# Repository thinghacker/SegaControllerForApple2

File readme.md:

# SegaControllerForApple2

Use a Sega Genesis/Megadrive Gamepad with your Apple 2 Computer

This repo contains the PCB details and Arduino code to be able to connect a 3 or 6 button Sega Genesis or Megadrive Gamepad to an Apple 2 Computer which utilises and Arduino Nano v3 and uses Sega Controller code by [Jon Thysell](https://github.com/jonthysell/SegaController) 

[PCB Details including Bill of Materials](pcb)

[Arduino Source Code](source)

## Theory of Operation
Apple 2 computers use two RC timer circuits to determine the position of each joystick axis. The capacitors are within the Apple 2 itself, while the resistors are variable potentiometers within the joystick.  Apple 2 computers expect the joystick to have two 150KOhm pots for X (0 = Left, 150K = Right) and Y (0 = Up, 150K = Down)

This board uses two daisy-chained MCP42100s as a means to create a 200K pot for X and Y (software limit this to 150K +/- any calibration offsets).  As this is an analog circuit, characteristics of the circuitry probably has been changed since the Apple 2 came from the factory, meaning that it is generally necessary to include an offset to wanted values for proper centering (similar to the trimmer capability on original Apple analog sticks) 

The Arduino reads the Sega Gamepad and sets the pot values to simulate analog behavior depending on the emulated joystick mode and previous states (there is a digital mode two analog styles and a hybrid mode which are selectable by clicking the Sega Controller Start Button)

Transistors are uses as switches by the arduino to trigger firebutton 0 and 1 (the method used is based on the [diagram](http://apple2.org.za/gswv/a2zine/faqs/R030PCA2RF.GIF) which was originally posted at in the official Csa2 (comp.sys.apple2) Usenet newsgroup Apple II FAQs)

If installed, the OLED provides visual feedback into the joystick operational mode and indication as to the joystick fire button and analog pot positions.

Audible feedback is also provided through the Piezo Buzzer which can be helpful when executing changes in the middle of a game.

### Gamepad Button Functions

|Button              | Game Pad Mode  | When C is Held Down |
| ------------ | ------------ |------------ |
| A | Firebutton 0 | Firebutton 0 Auto Fire Toggle | 
| B | Firebutton 1 | Firebutton 1 Auto Fire Toggle |
| C | Return Joystick Axes to Centre | |
| Start | Cycle Gamepad modes (Digital, Analog1, Analog2, Hybrid) | Enter Calibration Mode|
| X | Not Used |  |
| Y | Not Used |  |
| Z | Not Used |  |
| Mode | Not Used |  |

#### Notes:
Holding A/B/C together to swap Firebutton 0 and Firebutton 1

While Analog1, Analog2 and Hybrid do not re-centre when the Dpad buttons are released, pressing button C will recentre the stick.

## Calibration Mode

holding <strong>C</strong> and pressing <strong>Start</strong> on the controller will enable calibration mode.

Using the Dpad, the centre offset can be adjusted as necessary. Pressing <strong>Start</strong> will save the calibration offsets into the Arduino EEPROM and return to normal joystick mode

[ComputerInspector (MECC 1.0)](https://ftp.apple.asimov.net/images/disk_utils/diagnostics/ComputerInspector%20%28MECC%201.0%29.dsk) located on Asimov has a joystick test program which is useful to check joystick operation and to calibrate the joystick centre

If you are unable to download and install the image, the short Applesoft basic program below can be used to verify the board and code is working as expected and to support calibration efforts (when centred, the computer should be reporting X=128, Y=128)

###  Basic Joystick Test program from comp.sys.apple2 Apple II FAQ:
```
20 PRINT "X= "; PDL(0); TAB(15); "Y= ";PDL(1); TAB(30);
30 IF PEEK(49249)>127 THEN PRINT "  B0";
40 IF PEEK(49250)>127 THEN PRINT "  B1";
50 PRINT: GOTO 20
```

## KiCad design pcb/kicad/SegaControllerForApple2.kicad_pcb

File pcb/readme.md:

# SegaControllerForApple2

## PCB
This is a two layer through hole design.  It was made using [Kicad](http://kicad-pcb.org/) with the associated PCB source in the projects [Kicad](kicad) directory.  Gerber files are in the projects [Gerber](gerber) directory

### Assembled PCB

Epoxy resin was applied in and around the DB9 connector of the Apple 2 Facing cable to reduce the possibility of breaking wires from the connector.

### PCB Without OLED but with Piezo Speaker

### PCB Top Layer

### PCB Bottom Layer

## Bill of Materials

|Designation              | Item    | Description |
| ------------ | ------------ |------------ |
| U1 | Ardunio Nano v3 | Controller for the system | 
| U2 | Microchip MCP42100 |Dual 100K SPI controlled Pot|
| U3 | Microchip MCP42100 |Dual 100K SPI controlled Pot|
| R1 | 680 Ohm Resistor | Resistor |
| R2 | 1K Ohm Resistor | Resistor |
| R3 | 680 Ohm Resistor | Resistor |
| R4 | 1K Ohm Resistor | Resistor |
| Q1 | BC557 Transistor| PNP Transistor |
| Q2 | BC557 Transistor| PNP Transistor |
| J1 | DB9 Male Right Angle PCB Mount Socket | Connects to Sega Gamepad |
| J2 | IDC-10 Right Angle PCB Mount Connector | Apple 2 Gameport Cable Connector |
| J3 | 4x1 Row Connector (Socket)| OLED Display Connector |
| J4 | 4x1 Row Right Angle Connector (Pins)| A/D Breakout (Usually connecting to a Piezo Buzzer) |
| C1 | PC IDC-10 to DB9 Serial Breakout Cable (usually found as two connected to a computer card edge connector | Connects from PCB to Apple 2 Gameport |
| O1 | SH1106 1.3" OLED (Optional) | PCB Display |
| P1 | PC Speaker - Piezo Buzzer (Optional) | PCB Display |

### C1 - Typically Sourced on Card Edge Connector (Only 1 cable required)

### O1 - SH1106 1.3" OLED

### P1 - PC Speaker - Piezo Buzzer

## Construction Notes
This PCB does not require advanced soldering skills and can be assembled relatively quickly, however it may be best to work with an experienced friend or watch some youtube videos on build techniques if you are uncomfortable with soldering.

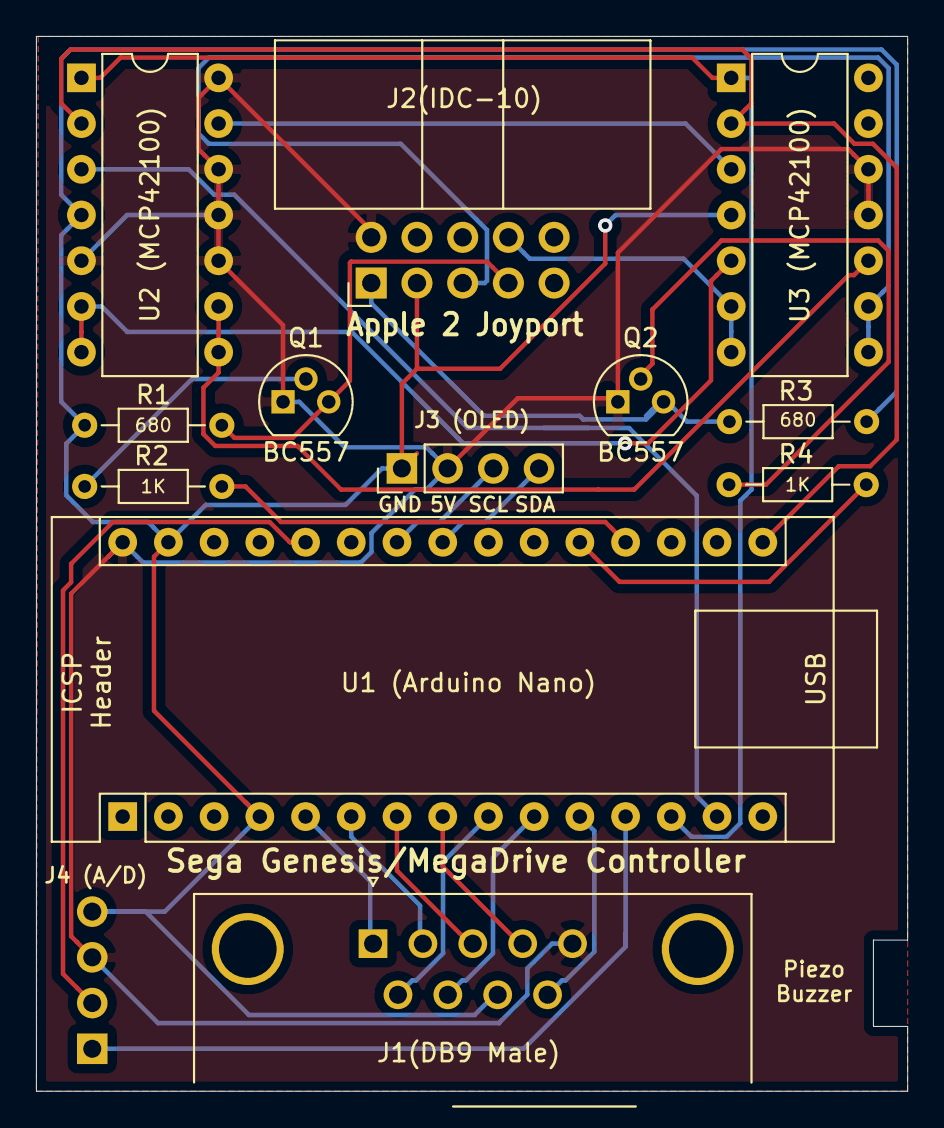
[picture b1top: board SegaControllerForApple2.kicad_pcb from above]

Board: 2 copper layers, 48.4 x 58.6 mm, 13 parts (1 on the bottom side), 27 nets.

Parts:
J1(DB9 Male): Conn_02x05_Odd_Even; DSUB-9_Male_Horizontal_P2.77x2.84mm_EdgePinOffset4.94mm_Hou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
J2(IDC-10): Conn_02x05_Odd_Even; IDC-Header_2x05_P2.54mm_Horizontal
J3(OLED)1: Conn_01x04_Female; PinHeader_1x04_P2.54mm_Vertical
J4(A/D_Breakout)1: Conn_01x04_Male; PinHeader_1x04_P2.54mm_Horizontal
Q1, Q2: BC557; TO-92
R1, R3: 680; R_Axial_DIN0204_L3.6mm_D1.6mm_P7.62mm_Horizontal
R2, R4: 1K; R_Axial_DIN0204_L3.6mm_D1.6mm_P7.62mm_Horizontal
U1: Arduino_Nano_v3.x; Arduino_Nano
U2: U2 (MCP42100); DIP-14_W7.62mm
U3: MCP42100; DIP-14_W7.62mm

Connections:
+5V: J1(DB9 Male).5, J2(IDC-10).2, J3(OLED)1.2, J4(A/D_Breakout)1.3, Q1.1, Q2.1, U1.30, U2.5, U2.10, U2.11, U2.12, U2.14, U3.11, U3.12
/PDL0: J2(IDC-10).5, U3.8, U3.9
/PDL1: J2(IDC-10).8, U3.6, U3.7
/SW0: J2(IDC-10).7, Q1.3, R1.1
/SW1: J2(IDC-10).1, Q2.3, R3.1
GND: J1(DB9 Male).8, J2(IDC-10).3, J3(OLED)1.1, J4(A/D_Breakout)1.4, R1.2, R3.2, U1.4, U1.29, U2.4, U3.4
unnamed: J1(DB9 Male).1, U1.5
unnamed: J1(DB9 Male).2, U1.6
unnamed: J1(DB9 Male).3, U1.7
unnamed: J1(DB9 Male).4, U1.8
unnamed: J1(DB9 Male).6, U1.9
unnamed: J1(DB9 Male).7, U1.10
unnamed: J1(DB9 Male).9, U1.11
unnamed: J3(OLED)1.3, U1.24
unnamed: J3(OLED)1.4, U1.23
unnamed: J4(A/D_Breakout)1.1, U1.12
unnamed: J4(A/D_Breakout)1.2, U1.26
unnamed: Q1.2, R2.2
unnamed: Q2.2, R4.2
unnamed: R2.1, U1.19
unnamed: R4.1, U1.20
unnamed: U1.13, U2.1, U3.1
unnamed: U1.14, U2.3
unnamed: U1.16, U2.2, U3.2
unnamed: U2.6, U2.7, U3.5
unnamed: U2.8, U2.9, U3.10
unnamed: U2.13, U3.3

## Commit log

2019-11-09 Hardware Version 1.2 is the new baseline
